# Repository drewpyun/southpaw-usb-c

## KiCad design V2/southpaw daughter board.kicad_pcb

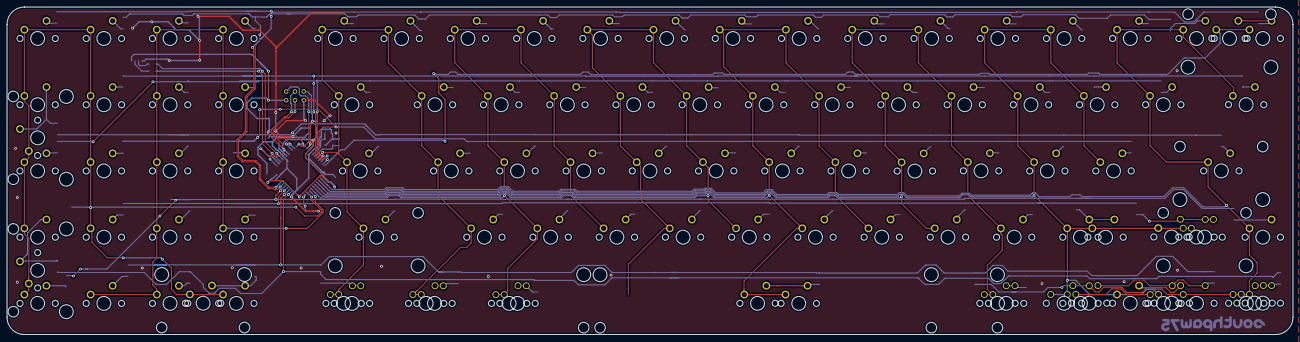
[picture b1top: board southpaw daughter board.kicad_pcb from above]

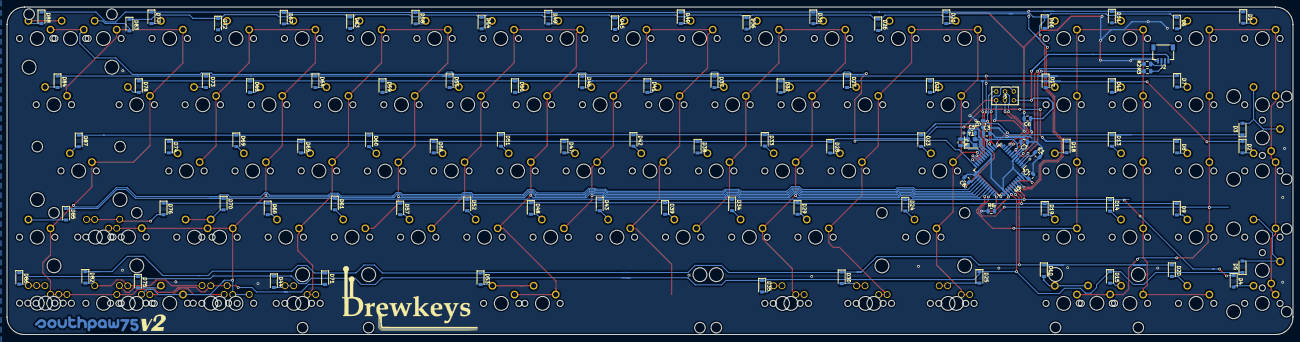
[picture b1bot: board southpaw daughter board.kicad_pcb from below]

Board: 2 copper layers, 369.9 x 94.2 mm, 202 parts (100 on the bottom side), 115 nets.

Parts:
C1, C2, C3, C8: 0.1uF; C_0805_2012Metric
C4, C5: 22p; C_0805_2012Metric
C6: 10uF; C_0805_2012Metric
C7: 1uF; C_0805_2012Metric
D1, D2, D3, D4, D5, D6, D7, D8, D9, D10, D11, D12, D13, D14, D15, D16, D17, D18, D19, D20, D21, D22, D23, D24, D25, D26, D27, D28, D29, D30, D31, D32, D33, D34, D35, D36, D37, D38, D39, D40, D41, D42, D43, D44, D45, D46, D47, D48, D49, D50, D51, D52, D53, D54, D55, D56, D57, D58, D59, D60, D61, D63, D64, D65, D66, D67, D68, D69, D70, D71, D72, D73, D74, D75, D76, D77, D78, D82, D83, D84, D85, D86, D87, D88: D_Small; D_SOD-123
J1: AVR-ISP-6; AVR-ISP
J2: SM04B-SRSS-TB(LF)(SN); JST-SR-4
MX1: num_+_2u; MXOnly-2U-NoLED
MX2: num_enter_2u; MXOnly-2U-NoLED
MX3: Numlck; MXOnly-1U-NoLED
MX4: num_+_extra; MXOnly-1U-NoLED
MX5: num_+_1u; MXOnly-1U-NoLED
MX6: num_enter_extra; MXOnly-1U-NoLED
MX7: num_enter_1u; MXOnly-1U-NoLED
MX8: num_/; MXOnly-1U-NoLED
MX9: num_7; MXOnly-1U-NoLED
MX10: num_4; MXOnly-1U-NoLED
MX11: num_1; MXOnly-1U-NoLED
MX12: num_.; MXOnly-1U-NoLED
MX13: num_0_2u; MXOnly-2U-ReversedStabilizers-NoLED
MX14: num_*; MXOnly-1U-NoLED
MX15: num_8; MXOnly-1U-NoLED
MX16: num_5; MXOnly-1U-NoLED
MX17: num_2; MXOnly-1U-NoLED
MX18: num_00_1u; MXOnly-1U-NoLED
MX19: num_-; MXOnly-1U-NoLED
MX20: num_9; MXOnly-1U-NoLED
MX21: num_6; MXOnly-1U-NoLED
MX22: num_3; MXOnly-1U-NoLED
MX23: num_0; MXOnly-1U-NoLED
MX24: LCTRL; MXOnly-1.25U-NoLED
MX25: ESC; MXOnly-1U-NoLED
MX26: TAB; MXOnly-1.5U-NoLED
MX27: CAPS; MXOnly-1.75U-NoLED
MX28: / 1.75 u; MXOnly-1.75U-NoLED
MX29: LCTRL 1.5u; MXOnly-1.5U-NoLED
MX30: LSHIFT; MXOnly-2.25U-NoLED
MX31: LWIN; MXOnly-1.25U-NoLED
MX32: 1; MXOnly-1U-NoLED
MX33: Q; MXOnly-1U-NoLED
MX34: A; MXOnly-1U-NoLED
MX35: Z; MXOnly-1U-NoLED
MX36: LWIN 1u; MXOnly-1U-NoLED
MX37: LALT; MXOnly-1.25U-NoLED
MX38: 2; MXOnly-1U-NoLED
MX39: W; MXOnly-1U-NoLED
MX40: S; MXOnly-1U-NoLED
MX41: X; MXOnly-1U-NoLED
MX42: LALT 1.5 u; MXOnly-1.5U-NoLED
MX43: 3; MXOnly-1U-NoLED
MX44: E; MXOnly-1U-NoLED
MX45: D; MXOnly-1U-NoLED
MX46: C; MXOnly-1U-NoLED
MX47: 4; MXOnly-1U-NoLED
MX48: R; MXOnly-1U-NoLED
MX49: F; MXOnly-1U-NoLED
MX50: V; MXOnly-1U-NoLED
MX51: 1u fn; MXOnly-1U-NoLED
MX52: 5; MXOnly-1U-NoLED
MX53: T; MXOnly-1U-NoLED
MX54: G; MXOnly-1U-NoLED
MX55: B; MXOnly-1U-NoLED
MX56: 6; MXOnly-1U-NoLED
MX57: Y; MXOnly-1U-NoLED
MX58: H; MXOnly-1U-NoLED
MX59: N; MXOnly-1U-NoLED
MX60: SPACE DEF; MXOnly-6.25U-ReversedStabilizers-NoLED
MX61: SPACE 7u; MXOnly-7U-ReversedStabilizers-NoLED
MX62: 7; MXOnly-1U-NoLED
MX63: U; MXOnly-1U-NoLED
MX64: J; MXOnly-1U-NoLED
MX65: M; MXOnly-1U-NoLED
MX66: 8; MXOnly-1U-NoLED
MX67: I; MXOnly-1U-NoLED
MX68: K; MXOnly-1U-NoLED
MX69: ,; MXOnly-1U-NoLED
MX71: 9; MXOnly-1U-NoLED
MX72: O; MXOnly-1U-NoLED
MX73: L; MXOnly-1U-NoLED
MX74: .; MXOnly-1U-NoLED
MX75: RALT; MXOnly-1.25U-NoLED
MX76: 0; MXOnly-1U-NoLED
MX77: P; MXOnly-1U-NoLED
MX78: ;; MXOnly-1U-NoLED
MX79: /; MXOnly-1U-NoLED
MX80: RALT 1.5 u; MXOnly-1.5U-NoLED
MX81: RWIN; MXOnly-1.25U-NoLED
MX82: -; MXOnly-1U-NoLED
MX83: [; MXOnly-1U-NoLED
MX84: '; MXOnly-1U-NoLED
MX85: RSHIFT; MXOnly-2.75U-NoLED
MX86: left 1u; MXOnly-1U-NoLED
MX87: RSHIFT 1.75u; MXOnly-1.75U-NoLED
MX88: DOWN 1u; MXOnly-1U-NoLED
MX89: =; MXOnly-1U-NoLED
MX90: ]; MXOnly-1U-NoLED
MX92: up; MXOnly-1U-NoLED
MX93: FN; MXOnly-1.25U-NoLED
MX94: RIGHT 1u; MXOnly-1U-NoLED
MX95: RCTRL; MXOnly-1.25U-NoLED
MX96: bsp extra; MXOnly-1U-NoLED
MX97: \; MXOnly-1.5U-NoLED
MX98: ENTER; MXOnly-2.25U-NoLED
MX99: RSHIFT extra; MXOnly-1U-NoLED
MX100: RCTRL 1.5 u; MXOnly-1.5U-NoLED
MX101: 1u del; MXOnly-1U-NoLED
MX102: bsp 2u; MXOnly-2U-NoLED
MX103: bsp 1u; MXOnly-1U-NoLED
MX104: win 1u; MXOnly-1U-NoLED
R1, R6: 10k; R_0805_2012Metric
R2, R3: 22; R_0805_2012Metric
U1: ATmega32U4-AU; TQFP-44_10x10mm_P0.8mm
Y1: 16MHz; Crystal_SMD_3225-4Pin_3.2x2.5mm

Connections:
+5V: C1.1, C2.1, C3.1, C6.1, C8.1, J2.1, R1.1, U1.2, U1.7, U1.14, U1.24, U1.34, U1.44
D+: J2.3, R2.2
D-: J2.2, R3.2
GND: C1.2, C2.2, C3.2, C4.1, C5.1, C6.2, C7.1, C8.2, J2.4, R6.1, U1.5, U1.15, U1.23, U1.35, U1.43, Y1.2, Y1.4
unnamed: C4.2, U1.17, Y1.1
unnamed: C5.2, U1.16, Y1.3
unnamed: C7.2, U1.6
unnamed: D1.2, MX3.2
unnamed: D2.2, MX4.2
unnamed: D3.2, MX1.2, MX5.2
unnamed: D4.2, MX6.2
unnamed: D5.2, MX2.2, MX7.2
unnamed: D6.2, MX8.2
unnamed: D7.2, MX9.2
unnamed: D8.2, MX10.2
unnamed: D9.2, MX11.2
unnamed: D10.2, MX13.2, MX23.2
unnamed: D11.2, MX14.2
unnamed: D12.2, MX15.2
unnamed: D13.2, MX16.2
unnamed: D14.2, MX17.2
unnamed: D15.2, MX18.2
unnamed: D16.2, MX19.2
unnamed: D17.2, MX20.2
unnamed: D18.2, MX21.2
unnamed: D19.2, MX22.2
unnamed: D20.2, MX12.2
unnamed: D21.2, MX25.2
unnamed: D22.2, MX26.2
unnamed: D23.2, MX27.2
unnamed: D24.2, MX30.2
unnamed: D25.2, MX24.2, MX29.2
unnamed: D26.2, MX32.2
unnamed: D27.2, MX33.2
unnamed: D28.2, MX34.2
unnamed: D29.2, MX35.2
unnamed: D30.2, MX31.2, MX36.2
unnamed: D31.2, MX38.2
unnamed: D32.2, MX39.2
unnamed: D33.2, MX40.2
unnamed: D34.2, MX41.2
unnamed: D35.2, MX37.2, MX42.2
unnamed: D36.2, MX43.2
unnamed: D37.2, MX44.2
unnamed: D38.2, MX45.2
unnamed: D39.2, MX46.2
unnamed: D40.2, MX47.2
unnamed: D41.2, MX48.2
unnamed: D42.2, MX49.2
unnamed: D43.2, MX50.2
unnamed: D44.2, MX51.2, MX75.2
unnamed: D45.2, MX52.2
unnamed: D46.2, MX53.2
unnamed: D47.2, MX54.2
unnamed: D48.2, MX55.2
unnamed: D49.2, MX56.2
unnamed: D50.2, MX57.2
unnamed: D51.2, MX58.2
unnamed: D52.2, MX59.2
unnamed: D53.2, MX60.2, MX61.2
unnamed: D54.2, MX62.2
unnamed: D55.2, MX63.2
unnamed: D56.2, MX64.2
unnamed: D57.2, MX65.2
unnamed: D58.2, MX66.2
unnamed: D59.2, MX67.2
unnamed: D60.2, MX68.2
unnamed: D61.2, MX69.2
unnamed: D63.2, MX71.2
unnamed: D64.2, MX72.2
unnamed: D65.2, MX73.2
unnamed: D66.2, MX74.2
unnamed: D67.2, MX76.2
unnamed: D68.2, MX77.2
unnamed: D69.2, MX78.2
unnamed: D70.2, MX28.2, MX79.2
unnamed: D71.2, MX80.2, MX93.2, MX101.2
unnamed: D72.2, MX82.2
unnamed: D73.2, MX83.2
unnamed: D74.2, MX84.2
unnamed: D75.2, MX86.2
unnamed: D76.2, MX85.2, MX87.2, MX92.2
unnamed: D77.2, MX89.2
unnamed: D78.2, MX90.2
unnamed: D82.2, MX81.2, MX88.2, MX104.2
unnamed: D83.2, MX96.2
unnamed: D84.2, MX97.2
unnamed: D85.2, MX99.2
unnamed: D86.2, MX94.2, MX95.2, MX100.2
unnamed: D87.2, MX98.2
unnamed: D88.2, MX102.2, MX103.2
unnamed: R2.1, U1.4
unnamed: R3.1, U1.3
unnamed: R6.2, U1.33
RST: R1.2, U1.13
col0: MX1.1, MX2.1, MX3.1, MX4.1, MX5.1, MX6.1, MX7.1, MX8.1, MX9.1, MX10.1, MX11.1, MX13.1, MX23.1, U1.32
col1: MX12.1, MX14.1, MX15.1, MX16.1, MX17.1, MX18.1, MX19.1, MX20.1, MX21.1, MX22.1, U1.31
col2: MX24.1, MX25.1, MX26.1, MX27.1, MX29.1, MX30.1, MX31.1, MX32.1, MX33.1, MX34.1, MX35.1, MX36.1, U1.18
col3: MX37.1, MX38.1, MX39.1, MX40.1, MX41.1, MX42.1, MX43.1, MX44.1, MX45.1, MX46.1, U1.30
col4: MX47.1, MX48.1, MX49.1, MX50.1, MX52.1, MX53.1, MX54.1, MX55.1, U1.29
col5: MX56.1, MX57.1, MX58.1, MX59.1, MX60.1, MX61.1, MX62.1, MX63.1, MX64.1, MX65.1, U1.28
col6: MX51.1, MX66.1, MX67.1, MX68.1, MX69.1, MX71.1, MX72.1, MX73.1, MX74.1, MX75.1, U1.27
col7: MX28.1, MX76.1, MX77.1, MX78.1, MX79.1, MX80.1, MX82.1, MX83.1, MX84.1, MX85.1, MX86.1, MX87.1, MX92.1, MX93.1, MX101.1, U1.26
col8: MX81.1, MX88.1, MX89.1, MX90.1, MX94.1, MX95.1, MX96.1, MX97.1, MX98.1, MX99.1, MX100.1, MX104.1, U1.25
col9: MX102.1, MX103.1, U1.22
row00: D1.1, D11.1, D21.1, D31.1, D40.1, D49.1, D58.1, D67.1, D77.1, D88.1, U1.40
row01: D6.1, D16.1, D26.1, D36.1, D45.1, D54.1, D63.1, D72.1, D83.1, U1.41
row10: D2.1, D12.1, D22.1, D32.1, D41.1, D50.1, D59.1, D68.1, D78.1, U1.20
row11: D7.1, D17.1, D27.1, D37.1, D46.1, D55.1, D64.1, D73.1, D84.1, U1.21
row20: D3.1, D13.1, D23.1, D33.1, D42.1, D51.1, D60.1, D69.1, D87.1, U1.12
row21: D8.1, D18.1, D28.1, D38.1, D47.1, D56.1, D65.1, D74.1, U1.19
row30: D4.1, D14.1, D24.1, D34.1, D43.1, D52.1, D61.1, D70.1, D85.1, U1.39
row31: D9.1, D19.1, D29.1, D39.1, D48.1, D57.1, D66.1, D76.1, U1.38
row40: D5.1, D15.1, D25.1, D35.1, D44.1, D75.1, D86.1, U1.36
row41: D10.1, D20.1, D30.1, D53.1, D71.1, D82.1, U1.37

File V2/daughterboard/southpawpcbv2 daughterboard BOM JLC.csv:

Item #,Designator,Qty,Mfg Part #,Description / Value,Footprint,Notes
,"C1,C2,C3,C8",4,CC0805KRX7R9BB104,0.1uF,Capacitor_SMD:C_0805_2012Metric,
,"C4,C5",2,CL21C220JBANNNC,22pF,Capacitor_SMD:C_0805_2012Metric,
,C6,1,CL21A106KAYNNNE,10uF,Capacitor_SMD:C_0805_2012Metric,
,C7,1,CL21B105KBFNNNE,1uF,Capacitor_SMD:C_0805_2012Metric,
,"D1,D2,D3,D4,D5,D6,D7,D8,D9,D10,D11,D12,D13,D14,D15,D16,D17,D18,D19,D20,D21,D22,D23,D24,D25,D26,D27,D28,D29,D30,D31,D32,D33,D34,D35,D36,D37,D38,D39,D40,D41,D42,D43,D44,D45,D46,D47,D48,D49,D50,D51,D52,D53,D54,D55,D56,D57,D58,D59,D60,D61,D63,D64,D65,D66,D67,D68,D69,D70,D71,D72,D73,D74,D75,D76,D77,D78,D82,D83,D84,D85,D86,D87,D88",88,SM4007PL,,Diode_SMD:D_SOD-123,
,J1,1,,,AVR 6 pin library:AVR-ISP,AVR-ISP-6 holes
,MX1,1,,,MX_Only:MXOnly-2U-NoLED,
,MX10,1,,,MX_Only:MXOnly-1U-NoLED,
,MX100,1,,,MX_Only:MXOnly-1.5U-NoLED,
,MX51,1,,,MX_Only:MXOnly-1U-NoLED,
,MX101,1,,,MX_Only:MXOnly-1U-NoLED,
,MX102,1,,,MX_Only:MXOnly-2U-NoLED,
,MX103,1,,,MX_Only:MXOnly-1U-NoLED,
,MX104,1,,,MX_Only:MXOnly-1U-NoLED,
,MX11,1,,,MX_Only:MXOnly-1U-NoLED,
,MX12,1,,,MX_Only:MXOnly-1U-NoLED,
,MX13,1,,,MX_Only:MXOnly-2U-NoLED,
,MX14,1,,,MX_Only:MXOnly-1U-NoLED,
,MX15,1,,,MX_Only:MXOnly-1U-NoLED,
,MX16,1,,,MX_Only:MXOnly-1U-NoLED,
,MX17,1,,,MX_Only:MXOnly-1U-NoLED,
,MX18,1,,,MX_Only:MXOnly-1U-NoLED,
,MX19,1,,,MX_Only:MXOnly-1U-NoLED,
,MX2,1,,,MX_Only:MXOnly-2U-NoLED,
,MX20,1,,,MX_Only:MXOnly-1U-NoLED,
,MX21,1,,,MX_Only:MXOnly-1U-NoLED,
,MX22,1,,,MX_Only:MXOnly-1U-NoLED,
,MX23,1,,,MX_Only:MXOnly-1U-NoLED,
,MX24,1,,,MX_Only:MXOnly-1.25U-NoLED,
,MX25,1,,,MX_Only:MXOnly-1U-NoLED,
,MX26,1,,,MX_Only:MXOnly-1.5U-NoLED,
,MX27,1,,,MX_Only:MXOnly-1.75U-NoLED,
,MX28,1,,,MX_Only:MXOnly-1.75U-NoLED,
,MX29,1,,,MX_Only:MXOnly-1.5U-NoLED,
,MX3,1,,,MX_Only:MXOnly-1U-NoLED,
,MX30,1,,,MX_Only:MXOnly-2.25U-NoLED,
,MX31,1,,,MX_Only:MXOnly-1.25U-NoLED,
,MX32,1,,,MX_Only:MXOnly-1U-NoLED,
,MX33,1,,,MX_Only:MXOnly-1U-NoLED,
,MX34,1,,,MX_Only:MXOnly-1U-NoLED,
,MX35,1,,,MX_Only:MXOnly-1U-NoLED,
,MX36,1,,,MX_Only:MXOnly-1U-NoLED,
,MX37,1,,,MX_Only:MXOnly-1.25U-NoLED,
,MX38,1,,,MX_Only:MXOnly-1U-NoLED,
,MX39,1,,,MX_Only:MXOnly-1U-NoLED,
,MX4,1,,,MX_Only:MXOnly-1U-NoLED,
,MX40,1,,,MX_Only:MXOnly-1U-NoLED,
,MX41,1,,,MX_Only:MXOnly-1U-NoLED,
,MX42,1,,,MX_Only:MXOnly-1.5U-NoLED,
,MX43,1,,,MX_Only:MXOnly-1U-NoLED,
,MX44,1,,,MX_Only:MXOnly-1U-NoLED,
,MX45,1,,,MX_Only:MXOnly-1U-NoLED,
,MX46,1,,,MX_Only:MXOnly-1U-NoLED,
,MX47,1,,,MX_Only:MXOnly-1U-NoLED,
,MX48,1,,,MX_Only:MXOnly-1U-NoLED,
,MX49,1,,,MX_Only:MXOnly-1U-NoLED,
,MX5,1,,,MX_Only:MXOnly-1U-NoLED,
,MX50,1,,,MX_Only:MXOnly-1U-NoLED,
,MX52,1,,,MX_Only:MXOnly-1U-NoLED,
,MX53,1,,,MX_Only:MXOnly-1U-NoLED,
,MX54,1,,,MX_Only:MXOnly-1U-NoLED,
,MX55,1,,,MX_Only:MXOnly-1U-NoLED,
,MX56,1,,,MX_Only:MXOnly-1U-NoLED,
,MX57,1,,,MX_Only:MXOnly-1U-NoLED,
,MX58,1,,,MX_Only:MXOnly-1U-NoLED,
,MX59,1,,,MX_Only:MXOnly-1U-NoLED,
,MX6,1,,,MX_Only:MXOnly-1U-NoLED,
,MX60,1,,,MX_Only:MXOnly-6.25U-ReversedStabilizers-NoLED,
,MX61,1,,,MX_Only:MXOnly-7U-ReversedStabilizers-NoLED,
,MX62,1,,,MX_Only:MXOnly-1U-NoLED,
,MX63,1,,,MX_Only:MXOnly-1U-NoLED,
,MX64,1,,,MX_Only:MXOnly-1U-NoLED,
,MX65,1,,,MX_Only:MXOnly-1U-NoLED,
,MX66,1,,,MX_Only:MXOnly-1U-NoLED,
,MX67,1,,,MX_Only:MXOnly-1U-NoLED,
,MX68,1,,,MX_Only:MXOnly-1U-NoLED,
,MX69,1,,,MX_Only:MXOnly-1U-NoLED,
,MX7,1,,,MX_Only:MXOnly-1U-NoLED,
,MX71,1,,,MX_Only:MXOnly-1U-NoLED,
,MX72,1,,,MX_Only:MXOnly-1U-NoLED,
,MX73,1,,,MX_Only:MXOnly-1U-NoLED,
,MX74,1,,,MX_Only:MXOnly-1U-NoLED,
,MX75,1,,,MX_Only:MXOnly-1.25U-NoLED,
,MX76,1,,,MX_Only:MXOnly-1U-NoLED,
,MX77,1,,,MX_Only:MXOnly-1U-NoLED,
,MX78,1,,,MX_Only:MXOnly-1U-NoLED,
,MX79,1,,,MX_Only:MXOnly-1U-NoLED,
,MX8,1,,,MX_Only:MXOnly-1U-NoLED,
,MX80,1,,,MX_Only:MXOnly-1.5U-NoLED,
,MX81,1,,,MX_Only:MXOnly-1.25U-NoLED,
,MX82,1,,,MX_Only:MXOnly-1U-NoLED,
,MX83,1,,,MX_Only:MXOnly-1U-NoLED,
,MX84,1,,,MX_Only:MXOnly-1U-NoLED,
,MX85,1,,,MX_Only:MXOnly-2.75U-NoLED,
,MX86,1,,,MX_Only:MXOnly-1U-NoLED,
,MX87,1,,,MX_Only:MXOnly-1.75U-NoLED,
,MX88,1,,,MX_Only:MXOnly-1U-NoLED,
,MX89,1,,,MX_Only:MXOnly-1U-NoLED,
,MX9,1,,,MX_Only:MXOnly-1U-NoLED,
,MX90,1,,,MX_Only:MXOnly-1U-NoLED,
,MX92,1,,,MX_Only:MXOnly-1U-NoLED,
,MX93,1,,,MX_Only:MXOnly-1.25U-NoLED,
,MX94,1,,,MX_Only:MXOnly-1U-NoLED,
,MX95,1,,,MX_Only:MXOnly-1.25U-NoLED,
,MX96,1,,,MX_Only:MXOnly-1U-NoLED,
,MX97,1,,,MX_Only:MXOnly-1.5U-NoLED,
,MX98,1,,,MX_Only:MXOnly-2.25U-NoLED,
,MX99,1,,,MX_Only:MXOnly-1U-NoLED,
,"R2,R3",2,0805W8F220JT5E,22,Resistor_SMD:R_0805_2012Metric,
,"R1,R6",2,0805W8F1002T5E,10k,Resistor_SMD:R_0805_2012Metric,
,SW1,1,TS-1187A-B-A-B,,Button_Switch_SMD:SW_SPST_TL3342,Reset
,U1,1,ATMEGA32U4-AU,Atmega32u4-AU,Package_QFP:TQFP-44_10x10mm_P0.8mm,ATmega32U4-AU
,USB1,1,TYPE-C-31-M-12,HRO-TYPE-C-31-M-12,Type-C:HRO-TYPE-C-31-M-12,HRO-TYPE-C-31-M-12
,Y1,1,X322516MLB4SI,16Mhz,Crystal:Crystal_SMD_3225-4Pin_3.2x2.5mm,
,J2,1,SM04B-SRSS-TB(LF)(SN),,JST-SR-4,4 pin JST connector

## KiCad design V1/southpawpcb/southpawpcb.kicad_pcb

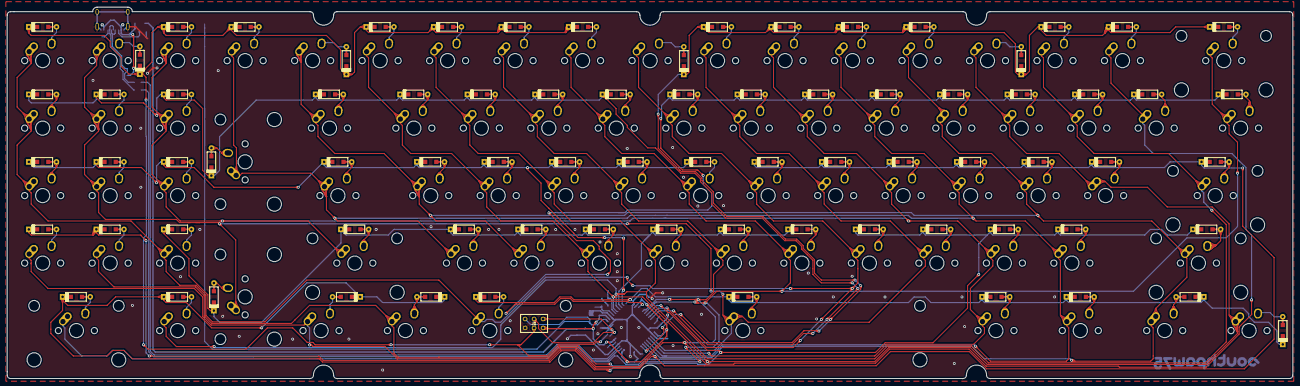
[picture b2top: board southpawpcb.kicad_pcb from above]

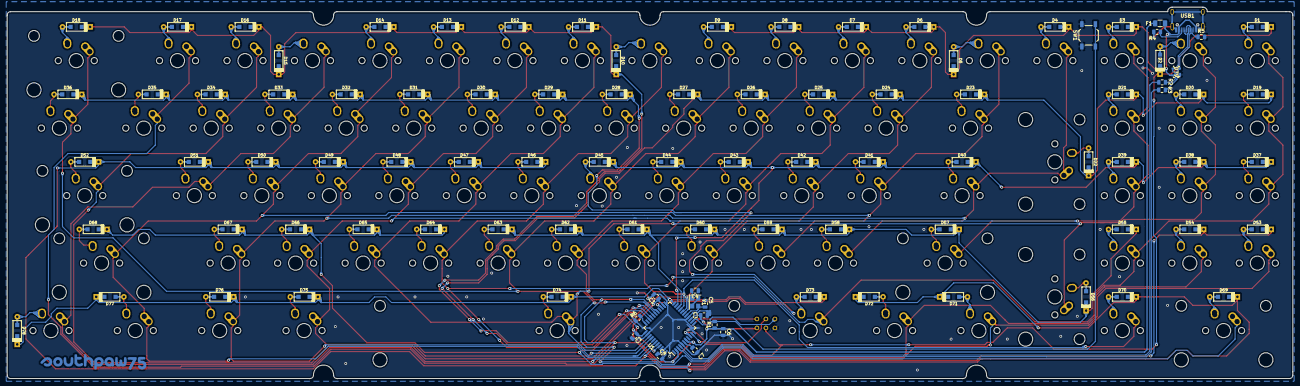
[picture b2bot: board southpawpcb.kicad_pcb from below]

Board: 2 copper layers, 362.9 x 104.8 mm, 177 parts (98 on the bottom side), 112 nets.

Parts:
C1, C2, C3, C8: 0.1uF; C_0805_2012Metric
C4, C5: 22p; C_0805_2012Metric
C6: 10uF; C_0805_2012Metric
C7: 1uF; C_0805_2012Metric
D1, D2, D3, D4, D5, D6, D7, D8, D9, D10, D11, D12, D13, D14, D15, D16, D17, D18, D19, D20, D21, D22, D23, D24, D25, D26, D27, D28, D29, D30, D31, D32, D33, D34, D35, D36, D37, D38, D39, D40, D41, D42, D43, D44, D45, D46, D47, D48, D49, D50, D51, D52, D53, D54, D55, D56, D57, D58, D59, D60, D61, D62, D63, D64, D65, D66, D67, D68, D69, D70, D71, D72, D73, D74, D75, D76, D77, D78: D; D_SOD123_axial-dual
D79: PRTR5V0U2X_215; TO-253-4
F1: 500mA; Fuse_1206_3216Metric
J1: AVR-ISP-6; AVR-ISP
K1, K2, K3, K4, K5, K6, K7, K8, K9, K10, K11, K12, K13, K14, K15, K16, K17, K19, K20, K21, K24, K25, K26, K27, K28, K29, K30, K31, K32, K33, K34, K35, K37, K38, K39, K41, K42, K43, K44, K45, K46, K47, K48, K49, K50, K51, K53, K54, K55, K58, K59, K60, K61, K62, K63, K64, K65, K66, K67, K70: KEYSW; MX-1U-NoLED
K18, K22, K56, K69: KEYSW; MX-2U-NoLED
K23, K36: KEYSW; MX-1.5U-NoLED
K40: KEYSW; MX-1.75U-NoLED
K52, K57: KEYSW; MX-2.25U-NoLED
K68: KEYSW; MX-2.75U-NoLED
K71, K72, K73, K75, K76, K77, K78: KEYSW; MX-1.25U-NoLED
K74: KEYSW; MX-6.25U-NoLED
R1, R6: 10k; R_0805_2012Metric
R2, R3: 22; R_0805_2012Metric
R4, R5: 5.1k; R_0805_2012Metric
SW1: Reset; SW_SPST_TL3342
U1: ATmega32U4-AU; TQFP-44_10x10mm_P0.8mm
USB1: HRO-TYPE-C-31-M-12
Y1: 16MHz; Crystal_SMD_3225-4Pin_3.2x2.5mm

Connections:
+5V: C1.1, C2.1, C3.1, C6.1, C8.1, F1.2, J1.VCC, R1.1, U1.2, U1.7, U1.14, U1.24, U1.34, U1.44
D+: D79.3, R2.2, USB1.6, USB1.8
D-: D79.2, R3.2, USB1.5, USB1.7
GND: C1.2, C2.2, C3.2, C4.1, C5.1, C6.2, C7.1, C8.2, D79.1, J1.GND, R4.2, R5.2, R6.1, SW1.1, U1.5, U1.15, U1.23, U1.35, U1.43, USB1.1, USB1.12, USB1.13, Y1.2, Y1.4
MISO: J1.MISO, U1.11
unnamed: C4.2, U1.17, Y1.1
unnamed: C5.2, U1.16, Y1.3
unnamed: C7.2, U1.6
unnamed: D1.2, K1.2
unnamed: D2.2, K2.2
unnamed: D3.2, K3.2
unnamed: D4.2, K4.2
unnamed: D5.2, K5.2
unnamed: D6.2, K6.2
unnamed: D7.2, K7.2
unnamed: D8.2, K8.2
unnamed: D9.2, K9.2
unnamed: D10.2, K10.2
unnamed: D11.2, K11.2
unnamed: D12.2, K12.2
unnamed: D13.2, K13.2
unnamed: D14.2, K14.2
unnamed: D15.2, K15.2
unnamed: D16.2, K16.2
unnamed: D17.2, K17.2
unnamed: D18.2, K18.2
unnamed: D19.2, K19.2
unnamed: D20.2, K20.2
unnamed: D21.2, K21.2
unnamed: D22.2, K22.2
unnamed: D23.2, K23.2
unnamed: D24.2, K24.2
unnamed: D25.2, K25.2
unnamed: D26.2, K26.2
unnamed: D27.2, K27.2
unnamed: D28.2, K28.2
unnamed: D29.2, K29.2
unnamed: D30.2, K30.2
unnamed: D31.2, K31.2
unnamed: D32.2, K32.2
unnamed: D33.2, K33.2
unnamed: D34.2, K34.2
unnamed: D35.2, K35.2
unnamed: D36.2, K36.2
unnamed: D37.2, K37.2
unnamed: D38.2, K38.2
unnamed: D39.2, K39.2
unnamed: D40.2, K40.2
unnamed: D41.2, K41.2
unnamed: D42.2, K42.2
unnamed: D43.2, K43.2
unnamed: D44.2, K44.2
unnamed: D45.2, K45.2
unnamed: D46.2, K46.2
unnamed: D47.2, K47.2
unnamed: D48.2, K48.2
unnamed: D49.2, K49.2
unnamed: D50.2, K50.2
unnamed: D51.2, K51.2
unnamed: D52.2, K52.2
unnamed: D53.2, K53.2
unnamed: D54.2, K54.2
unnamed: D55.2, K55.2
unnamed: D56.2, K56.2
unnamed: D57.2, K57.2
unnamed: D58.2, K58.2
unnamed: D59.2, K59.2
unnamed: D60.2, K60.2
unnamed: D61.2, K61.2
unnamed: D62.2, K62.2
unnamed: D63.2, K63.2
unnamed: D64.2, K64.2
unnamed: D65.2, K65.2
unnamed: D66.2, K66.2
unnamed: D67.2, K67.2
unnamed: D68.2, K68.2
unnamed: D69.2, K69.2
unnamed: D70.2, K70.2
unnamed: D71.2, K71.2
unnamed: D72.2, K72.2
unnamed: D73.2, K73.2
unnamed: D74.2, K74.2
unnamed: D75.2, K75.2
unnamed: D76.2, K76.2
unnamed: D77.2, K77.2
unnamed: D78.2, K78.2
unnamed: R2.1, U1.4
unnamed: R3.1, U1.3
unnamed: R4.1, USB1.10
unnamed: R5.1, USB1.4
unnamed: R6.2, U1.33
RST: J1.RST, R1.2, SW1.2, U1.13
SCK: J1.SCK, U1.9
VCC: D79.4, F1.1, USB1.2, USB1.11
col0: K1.1, K10.1, K19.1, K28.1, K37.1, K46.1, K55.1, K64.1, K73.1, U1.30
col1: K2.1, K11.1, K20.1, K29.1, K38.1, K47.1, K56.1, K65.1, K74.1, U1.36
col2: K3.1, K12.1, K21.1, K30.1, K39.1, K48.1, K57.1, K66.1, K75.1, U1.37
col3: K4.1, K13.1, K22.1, K31.1, K40.1, K49.1, K58.1, K67.1, K76.1, U1.38
col4: K5.1, K14.1, K23.1, K32.1, K41.1, K50.1, K59.1, K68.1, K77.1, U1.39
col5: K6.1, K15.1, K24.1, K33.1, K42.1, K51.1, K60.1, K69.1, K78.1, U1.18
col6: K7.1, K16.1, K25.1, K34.1, K43.1, K52.1, K61.1, K70.1, U1.19
col7: K8.1, K17.1, K26.1, K35.1, K44.1, K53.1, K62.1, K71.1, U1.27
col8: K9.1, K18.1, K27.1, K36.1, K45.1, K54.1, K63.1, K72.1, U1.28
row0: D1.1, D2.1, D3.1, D4.1, D5.1, D6.1, D7.1, D8.1, D9.1, J1.MOSI, U1.10
row1: D10.1, D11.1, D12.1, D13.1, D14.1, D15.1, D16.1, D17.1, D18.1, U1.41
row2: D19.1, D20.1, D21.1, D22.1, D23.1, D24.1, D25.1, D26.1, D27.1, U1.31
row3: D28.1, D29.1, D30.1, D31.1, D32.1, D33.1, D34.1, D35.1, D36.1, U1.25
row4: D37.1, D38.1, D39.1, D40.1, D41.1, D42.1, D43.1, D44.1, D45.1, U1.21
row5: D46.1, D47.1, D48.1, D49.1, D50.1, D51.1, D52.1, D53.1, D54.1, U1.40
row6: D55.1, D56.1, D57.1, D58.1, D59.1, D60.1, D61.1, D62.1, D63.1, U1.20
row7: D64.1, D65.1, D66.1, D67.1, D68.1, D69.1, D70.1, D71.1, D72.1, U1.29
row8: D73.1, D74.1, D75.1, D76.1, D77.1, D78.1, U1.22

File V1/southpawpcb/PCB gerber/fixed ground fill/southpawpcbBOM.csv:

Comment,Designator,Footprint,LCSC
"0.1uF","C1,C2,C3,C8","Capacitor_SMD:C_0805_2012Metric",""
"22p","C4,C5","Capacitor_SMD:C_0805_2012Metric",""
"10uF","C6","Capacitor_SMD:C_0805_2012Metric",""
"1uF","C7","Capacitor_SMD:C_0805_2012Metric",""
"D","D1,D2,D3,D4,D5,D6,D7,D8,D9,D10,D11,D12,D13,D14,D15,D16,D17,D18,D19,D20,D21,D22,D23,D24,D25,D26,D27,D28,D29,D30,D31,D32,D33,D34,D35,D36,D37,D38,D39,D40,D41,D42,D43,D44,D45,D46,D47,D48,D49,D50,D51,D52,D53,D54,D55,D56,D57,D58,D59,D60,D61,D62,D63,D64,D65,D66,D67,D68,D69,D70,D71,D72,D73,D74,D75,D76,D77,D78","Diode_SMD:D_SOD-123",""
"PRTR5V0U2X_215","D79","digikey-footprints:TO-253-4",""
"500mA","F1","Fuse:Fuse_1206_3216Metric",""
"AVR-ISP-6","J1","AVR 6 pin library:AVR-ISP",""
"KEYSW","K1,K2,K3,K4,K5,K6,K7,K8,K9,K10,K11,K12,K13,K14,K15,K16,K17,K19,K20,K21,K24,K25,K26,K27,K28,K29,K30,K31,K32,K33,K34,K35,K37,K38,K39,K41,K42,K43,K44,K45,K46,K47,K48,K49,K50,K51,K53,K54,K55,K58,K59,K60,K61,K62,K63,K64,K65,K66,K67,K70","MX/Alps_Hybrid:MX-1U-NoLED",""
"KEYSW","K18,K22,K56,K69","MX/Alps_Hybrid:MX-2U-NoLED",""
"KEYSW","K23,K36","MX/Alps_Hybrid:MX-1.5U-NoLED",""
"KEYSW","K40","MX/Alps_Hybrid:MX-1.75U-NoLED",""
"KEYSW","K52,K57","MX/Alps_Hybrid:MX-2.25U-NoLED",""
"KEYSW","K68","MX/Alps_Hybrid:MX-2.75U-NoLED",""
"KEYSW","K71,K72,K73,K75,K76,K77,K78","MX/Alps_Hybrid:MX-1.25U-NoLED",""
"KEYSW","K74","MX/Alps_Hybrid:MX-6.25U-NoLED",""
"22","R2,R3","Resistor_SMD:R_0805_2012Metric",""
"5.1k","R4,R5","Resistor_SMD:R_0805_2012Metric",""
"10k","R1,R6","Resistor_SMD:R_0805_2012Metric",""
"Reset","SW1","Button_Switch_SMD:SW_SPST_TL3342",""
"ATmega32U4-AU","U1","Package_QFP:TQFP-44_10x10mm_P0.8mm",""
"HRO-TYPE-C-31-M-12","USB1","Type-C:HRO-TYPE-C-31-M-12",""
"16MHz","Y1","Crystal:Crystal_SMD_3225-4Pin_3.2x2.5mm",""

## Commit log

2020-07-21 publish
2020-07-30 diagram
2020-09-27 HUGE commit read description
    fixed southpaw v1, added southpaw v1 GERBER, POS and BOM
    added southpaw v2, both daughterboard and and fr4 vers.
    added southpaw v2 fr4 GERBER, BOM and POS
    fr4 version BOM and POS optimized for pcbway, v1 optimized for JLC.
    added drewkeys logo
    changed folder formatting and optimized all files
2020-09-29 fixed crucial errors on both PCBS
    added and fixed gerbers/bom/pos for all
2020-10-09 fixed logo changed files added compat, ordered protos
2020-10-24 v2 update
    ordered protos and pending revisions
2020-11-04 final draft
    final upload ?
